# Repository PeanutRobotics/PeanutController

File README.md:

# Peanut Controller

**STM32N657L0 SoM for robotics applications with NN accelerator**

[Board Specification Spreadsheet](https://docs.google.com/spreadsheets/d/1FFwfozj1tVRQfzXSudWjYrMUlAaIKrv69ZutKTBa3as/edit?gid=110133492#gid=110133492)

## Specifications
- 8-layer PCB, 24×40x1 mm, 
- Processor:
    - STM32N6 MCU with Neural-ART accelerator
    - ESP32-C5HF4 for RF, connected to STM32 via UART
- Power:
    - Input: 3.5 ~ 4.3 V (LiPo) via `BAT_IN`
    - 3.3 V power output for external carrier and add-on boards via `3V3_AUX_OUT`
    - INA2227 monitors battery input and auxiliary output
- Onboard sensors:
    - IMU, Magnetometer, Barometer
- Interfaces via Board-to-Board connectors:
    - High speed: USB HS, Ethernet RMII, 2-lane MIPI CSI-2
    - Low speed: UART, I2C, SPI, FDCAN, DShot timer signals
    - Wireless: Wi-Fi 6 (2.4/5 GHz), BLE

## Detailed Specifications
### Processor
| MCU | Flash | RAM | Role | Description |
|-----|-----|-----|-----|-----|
| STM32N657L0H3Q | 128 MiB external OctoSPI NOR | 32 MiB external HexaSPI PSRAM | Main controller | Onboard Neural-ART accelerator |
| ESP32-C5HF4 | 4 MB in-package flash | 400 kB | RF companion | Dual-band Wi-Fi 6 |

### Connectivity
| Type | Name | Domain |
|----------|----------|----------|
| UART     | UART[1:6]  | J3 / J4 |
| SPI      | SPI[2:3]   | J1 / J2 |
| I2C      | I2C[1:3]   | J3 / J4 |
| FDCAN    | FDCAN[1:2] | J1 / J2 |
| DShot    | 8 timer signals (7 shared with UART) | J3 / J4 |
| USB HS   | USB        | J1 / J2 |
| Ethernet | RMII       | J1 / J2 |
| CSI      | MIPI CSI-2 | J5 |
| RF       | Wi-Fi 6 / BLE    | RF      |
| SWD      | SWDIO, SWCLK, NRST, 3.3 V reference, GND | TP1–TP5 |

### Onboard Sensors
| Sensor | Part Name |
|----------|---------|
| IMU          | LSM6DSV16XTR |
| Magnetometer | MMC5983MA |
| Barometer    | BMP581 |
| Power        | INA2227AIYBJR |

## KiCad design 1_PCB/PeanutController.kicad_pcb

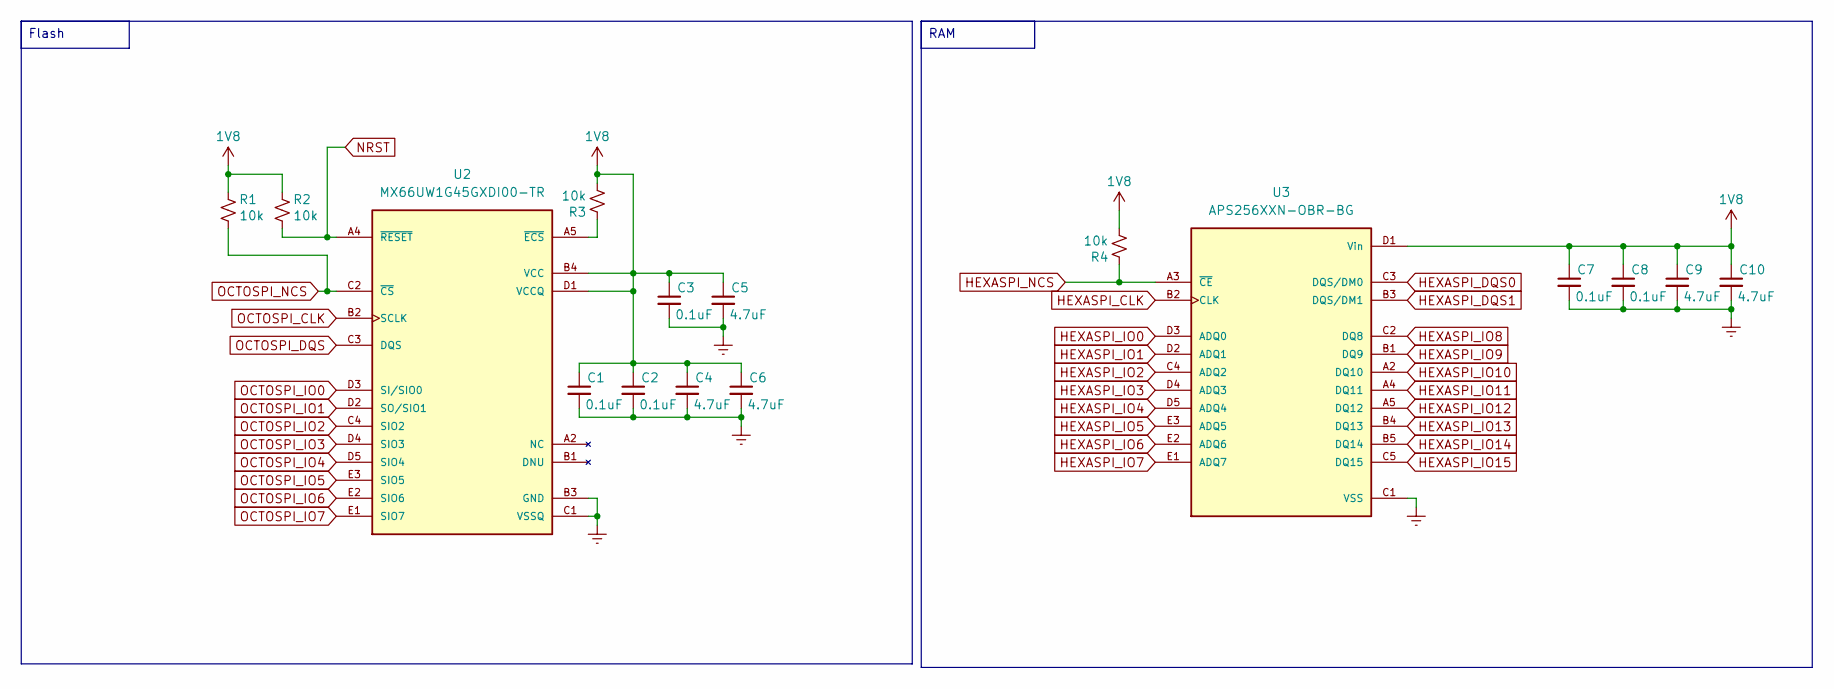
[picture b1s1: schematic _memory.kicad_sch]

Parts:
C1, C2, C3, C7, C8: 0.1uF; C_0402_1005Metric
C4, C5, C6: 4.7uF; C_0603_1608Metric
C9, C10: 4.7uF; C_0402_1005Metric
R1, R2, R3, R4: 10k; R_0402_1005Metric
U2: MX66UW1G45GXDI00-TR; BGA24C100P5X5_800X600X120; PARTREV 1.1
U3: APS256XXN-OBR-BG; BGA24C100P5X5_800X600X120; PARTREV 1.00

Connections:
1V8: C1.1, C2.1, C3.1, C4.1, C5.1, C6.1, C7.1, C8.1, C9.1, C10.1, R1.2, R2.2, R3.1, R4.1, U2.B4 (VCC), U2.D1 (VCCQ), U2.E4 (VCCQ), U3.D1 (Vin), U3.E4 (Vin); also elsewhere on the board
Earth: C1.2, C2.2, C3.2, C4.2, C5.2, C6.2, C7.2, C8.2, C9.2, C10.2, U2.B3 (GND), U2.C1 (VSSQ), U2.E5 (VSSQ), U3.C1 (VSS), U3.E5 (VSS); also elsewhere on the board
HEXASPI_CLK: U3.B2 (CLK); also elsewhere on the board
HEXASPI_DQS0: U3.C3 (DQS/DM0); also elsewhere on the board
HEXASPI_DQS1: U3.B3 (DQS/DM1); also elsewhere on the board
HEXASPI_IO0: U3.D3 (ADQ0); also elsewhere on the board
HEXASPI_IO1: U3.D2 (ADQ1); also elsewhere on the board
HEXASPI_IO2: U3.C4 (ADQ2); also elsewhere on the board
HEXASPI_IO3: U3.D4 (ADQ3); also elsewhere on the board
HEXASPI_IO4: U3.D5 (ADQ4); also elsewhere on the board
HEXASPI_IO5: U3.E3 (ADQ5); also elsewhere on the board
HEXASPI_IO6: U3.E2 (ADQ6); also elsewhere on the board
HEXASPI_IO7: U3.E1 (ADQ7); also elsewhere on the board
HEXASPI_IO8: U3.C2 (DQ8); also elsewhere on the board
HEXASPI_IO9: U3.B1 (DQ9); also elsewhere on the board
HEXASPI_IO10: U3.A2 (DQ10); also elsewhere on the board
HEXASPI_IO11: U3.A4 (DQ11); also elsewhere on the board
HEXASPI_IO12: U3.A5 (DQ12); also elsewhere on the board
HEXASPI_IO13: U3.B4 (DQ13); also elsewhere on the board
HEXASPI_IO14: U3.B5 (DQ14); also elsewhere on the board
HEXASPI_IO15: U3.C5 (DQ15); also elsewhere on the board
HEXASPI_NCS: R4.2, U3.A3 (~CE); also elsewhere on the board
NRST: R2.1, U2.A4 (~RESET); also elsewhere on the board
unnamed: R3.2, U2.A5 (~ECS)
OCTOSPI_CLK: U2.B2 (SCLK); also elsewhere on the board
OCTOSPI_DQS: U2.C3 (DQS); also elsewhere on the board
OCTOSPI_IO0: U2.D3 (SI/SIO0); also elsewhere on the board
OCTOSPI_IO1: U2.D2 (SO/SIO1); also elsewhere on the board
OCTOSPI_IO2: U2.C4 (SIO2); also elsewhere on the board
OCTOSPI_IO3: U2.D4 (SIO3); also elsewhere on the board
OCTOSPI_IO4: U2.D5 (SIO4); also elsewhere on the board
OCTOSPI_IO5: U2.E3 (SIO5); also elsewhere on the board
OCTOSPI_IO6: U2.E2 (SIO6); also elsewhere on the board
OCTOSPI_IO7: U2.E1 (SIO7); also elsewhere on the board
OCTOSPI_NCS: R1.1, U2.C2 (~CS); also elsewhere on the board

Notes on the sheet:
RAM
Flash

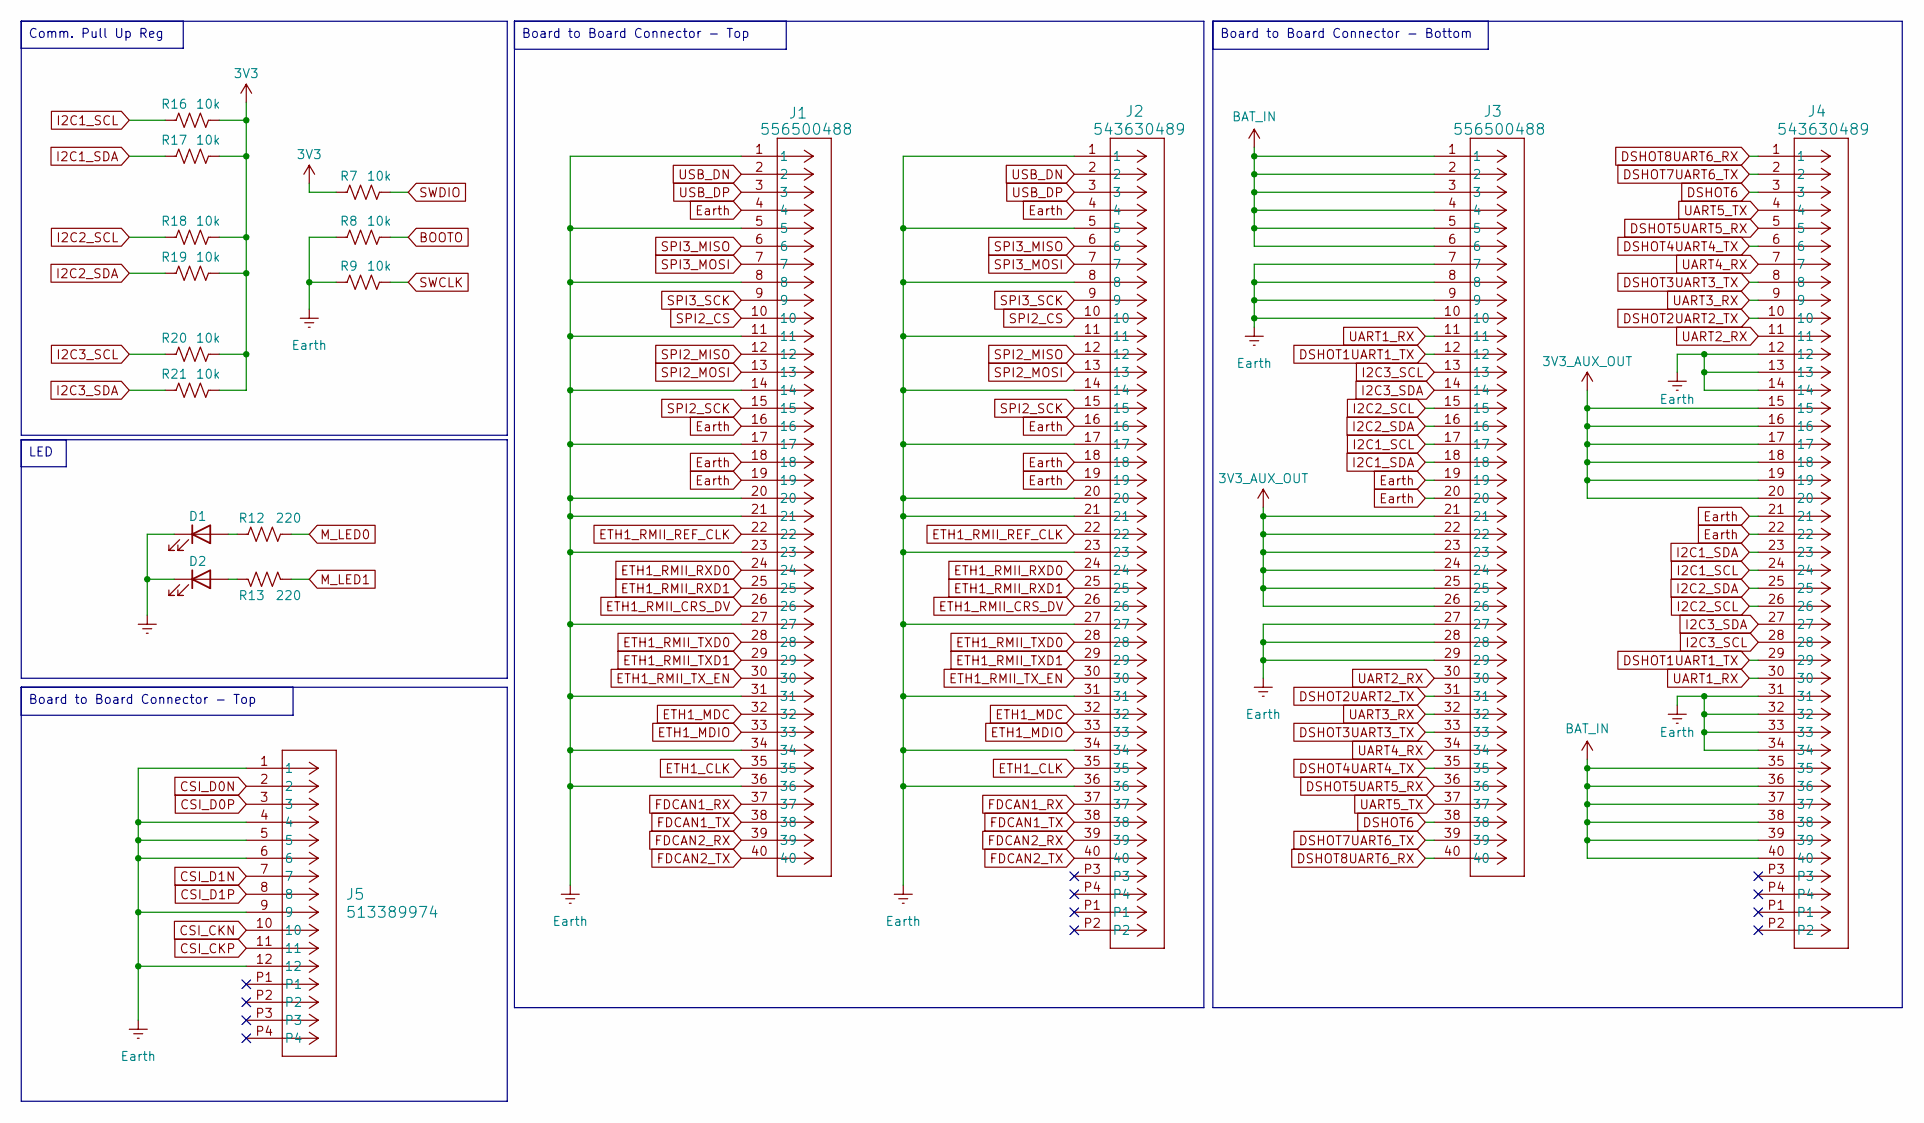
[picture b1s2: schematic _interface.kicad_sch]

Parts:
D1, D2: LED; LED_0603_1608Metric
J1, J3: 556500488; CON_556500488_MOL
J2, J4: 543630489; CON_543630489
J5: 513389974; CON_513389974
R7, R8, R9, R16, R17, R18, R19, R20, R21: 10k; R_0402_1005Metric
R12, R13: 220; R_0402_1005Metric

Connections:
3V3: R7.1, R16.2, R17.2, R18.2, R19.2, R20.2, R21.2; also elsewhere on the board
3V3_AUX_OUT: J3.21, J3.22, J3.23, J3.24, J3.25, J3.26, J4.15, J4.16, J4.17, J4.18, J4.19, J4.20; also elsewhere on the board
BAT_IN: J3.1, J3.2, J3.3, J3.4, J3.5, J3.6, J4.35, J4.36, J4.37, J4.38, J4.39, J4.40; also elsewhere on the board
BOOTO: R8.2; also elsewhere on the board
CSI_CKN: J5.10; also elsewhere on the board
CSI_CKP: J5.11; also elsewhere on the board
CSI_D0N: J5.2; also elsewhere on the board
CSI_D0P: J5.3; also elsewhere on the board
CSI_D1N: J5.7; also elsewhere on the board
CSI_D1P: J5.8; also elsewhere on the board
DSHOT1UART1_TX: J3.12, J4.29; also elsewhere on the board
DSHOT2UART2_TX: J3.31, J4.10; also elsewhere on the board
DSHOT3UART3_TX: J3.33, J4.8; also elsewhere on the board
DSHOT4UART4_TX: J3.35, J4.6; also elsewhere on the board
DSHOT5UART5_RX: J3.36, J4.5; also elsewhere on the board
DSHOT6: J3.38, J4.3; also elsewhere on the board
DSHOT7UART6_TX: J3.39, J4.2; also elsewhere on the board
DSHOT8UART6_RX: J3.40, J4.1; also elsewhere on the board
ETH1_CLK: J1.35, J2.35; also elsewhere on the board
ETH1_MDC: J1.32, J2.32; also elsewhere on the board
ETH1_MDIO: J1.33, J2.33; also elsewhere on the board
ETH1_RMII_CRS_DV: J1.26, J2.26; also elsewhere on the board
ETH1_RMII_REF_CLK: J1.22, J2.22; also elsewhere on the board
ETH1_RMII_RXD0: J1.24, J2.24; also elsewhere on the board
ETH1_RMII_RXD1: J1.25, J2.25; also elsewhere on the board
ETH1_RMII_TXD0: J1.28, J2.28; also elsewhere on the board
ETH1_RMII_TXD1: J1.29, J2.29; also elsewhere on the board
ETH1_RMII_TX_EN: J1.30, J2.30; also elsewhere on the board
Earth: D1.1 (K), D2.1 (K), J1.1, J1.4, J1.5, J1.8, J1.11, J1.14, J1.16, J1.17, J1.18, J1.19, J1.20, J1.21, J1.23, J1.27, J1.31, J1.34, J1.36, J2.1, J2.4, J2.5, J2.8, J2.11, J2.14, J2.16, J2.17, J2.18, J2.19, J2.20, J2.21, J2.23, J2.27, J2.31, J2.34, J2.36, J3.7, J3.8, J3.9, J3.10, J3.19, J3.20, J3.27, J3.28, J3.29, J4.12, J4.13, J4.14, J4.21, J4.22, J4.31, J4.32, J4.33, J4.34, J5.1, J5.4, J5.5, J5.6, J5.9, J5.12, R8.1, R9.1; also elsewhere on the board
FDCAN1_RX: J1.37, J2.37; also elsewhere on the board
FDCAN1_TX: J1.38, J2.38; also elsewhere on the board
FDCAN2_RX: J1.39, J2.39; also elsewhere on the board
FDCAN2_TX: J1.40, J2.40; also elsewhere on the board
I2C1_SCL: J3.17, J4.24, R16.1; also elsewhere on the board
I2C1_SDA: J3.18, J4.23, R17.1; also elsewhere on the board
I2C2_SCL: J3.15, J4.26, R18.1; also elsewhere on the board
I2C2_SDA: J3.16, J4.25, R19.1; also elsewhere on the board
I2C3_SCL: J3.13, J4.28, R20.1; also elsewhere on the board
I2C3_SDA: J3.14, J4.27, R21.1; also elsewhere on the board
M_LED0: R12.2
M_LED1: R13.2
unnamed: D1.2 (A), R12.1
unnamed: D2.2 (A), R13.1
SPI2_CS: J1.10, J2.10; also elsewhere on the board
SPI2_MISO: J1.12, J2.12; also elsewhere on the board
SPI2_MOSI: J1.13, J2.13; also elsewhere on the board
SPI2_SCK: J1.15, J2.15; also elsewhere on the board
SPI3_MISO: J1.6, J2.6; also elsewhere on the board
SPI3_MOSI: J1.7, J2.7; also elsewhere on the board
SPI3_SCK: J1.9, J2.9; also elsewhere on the board
SWCLK: R9.2; also elsewhere on the board
SWDIO: R7.2; also elsewhere on the board
UART1_RX: J3.11, J4.30; also elsewhere on the board
UART2_RX: J3.30, J4.11; also elsewhere on the board
UART3_RX: J3.32, J4.9; also elsewhere on the board
UART4_RX: J3.34, J4.7; also elsewhere on the board
UART5_TX: J3.37, J4.4; also elsewhere on the board
USB_DN: J1.2, J2.2; also elsewhere on the board
USB_DP: J1.3, J2.3; also elsewhere on the board

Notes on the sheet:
Comm. Pull Up Reg
Board to Board Connector - Top
Board to Board Connector - Bottom
LED

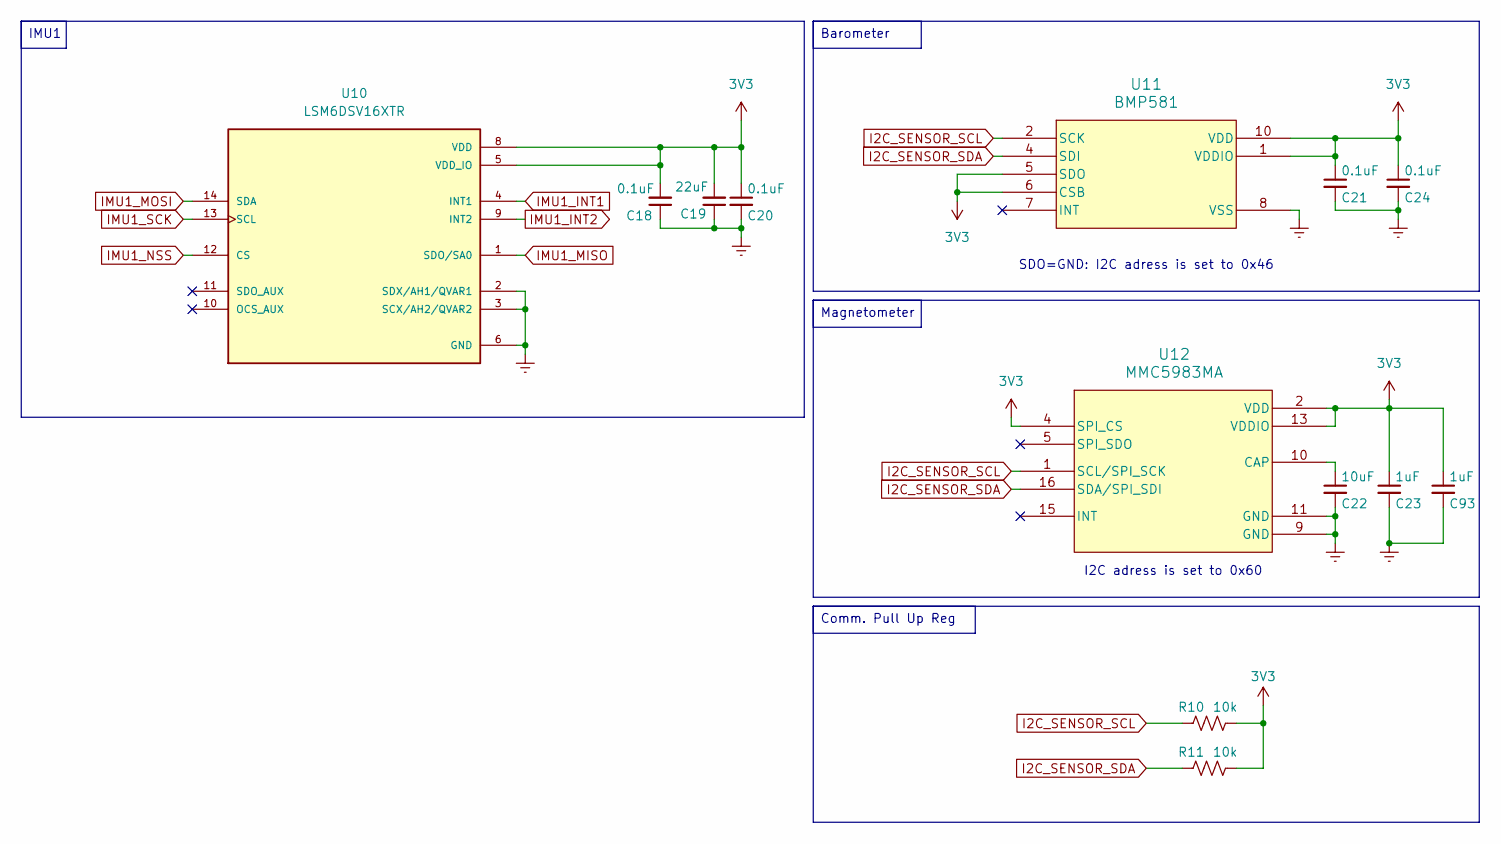
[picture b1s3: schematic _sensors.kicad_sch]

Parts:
C18, C20, C21, C24: 0.1uF; C_0402_1005Metric
C19: 22uF; C_0603_1608Metric
C22: 10uF; C_0402_1005Metric
C23, C93: 1uF; C_0402_1005Metric
R10, R11: 10k; R_0402_1005Metric
U10: LSM6DSV16XTR; XDCR_LSM6DSV16XTR; PARTREV 4
U11: BMP581; QFN10_BMP581_BOS
U12: MMC5983MA; MMC5983MA_MEM

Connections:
3V3: C18.2, C19.2, C20.1, C21.1, C23.1, C24.1, C93.1, R10.2, R11.2, U10.5 (VDD_IO), U10.8 (VDD), U11.1 (VDDIO), U11.5 (SDO), U11.6 (CSB), U11.10 (VDD), U12.2 (VDD), U12.4 (SPI_CS), U12.13 (VDDIO); also elsewhere on the board
Earth: C18.1, C19.1, C20.2, C21.2, C22.2, C23.2, C24.2, C93.2, U10.2 (SDX/AH1/QVAR1), U10.3 (SCX/AH2/QVAR2), U10.6 (GND), U10.7 (GND), U11.3 (VSS), U11.8 (VSS), U11.9 (VSS), U12.9 (GND), U12.11 (GND); also elsewhere on the board
I2C_SENSOR_SCL: R10.1, U11.2 (SCK), U12.1 (SCL/SPI_SCK); also elsewhere on the board
I2C_SENSOR_SDA: R11.1, U11.4 (SDI), U12.16 (SDA/SPI_SDI); also elsewhere on the board
IMU1_INT1: U10.4 (INT1)
IMU1_INT2: U10.9 (INT2); also elsewhere on the board
IMU1_MISO: U10.1 (SDO/SA0); also elsewhere on the board
IMU1_MOSI: U10.14 (SDA); also elsewhere on the board
IMU1_NSS: U10.12 (CS); also elsewhere on the board
IMU1_SCK: U10.13 (SCL); also elsewhere on the board
unnamed: C22.1, U12.10 (CAP)

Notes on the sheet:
I2C adress is set to 0x60
SDO=GND: I2C adress is set to 0x46
IMU1
Comm. Pull Up Reg
Magnetometer
Barometer

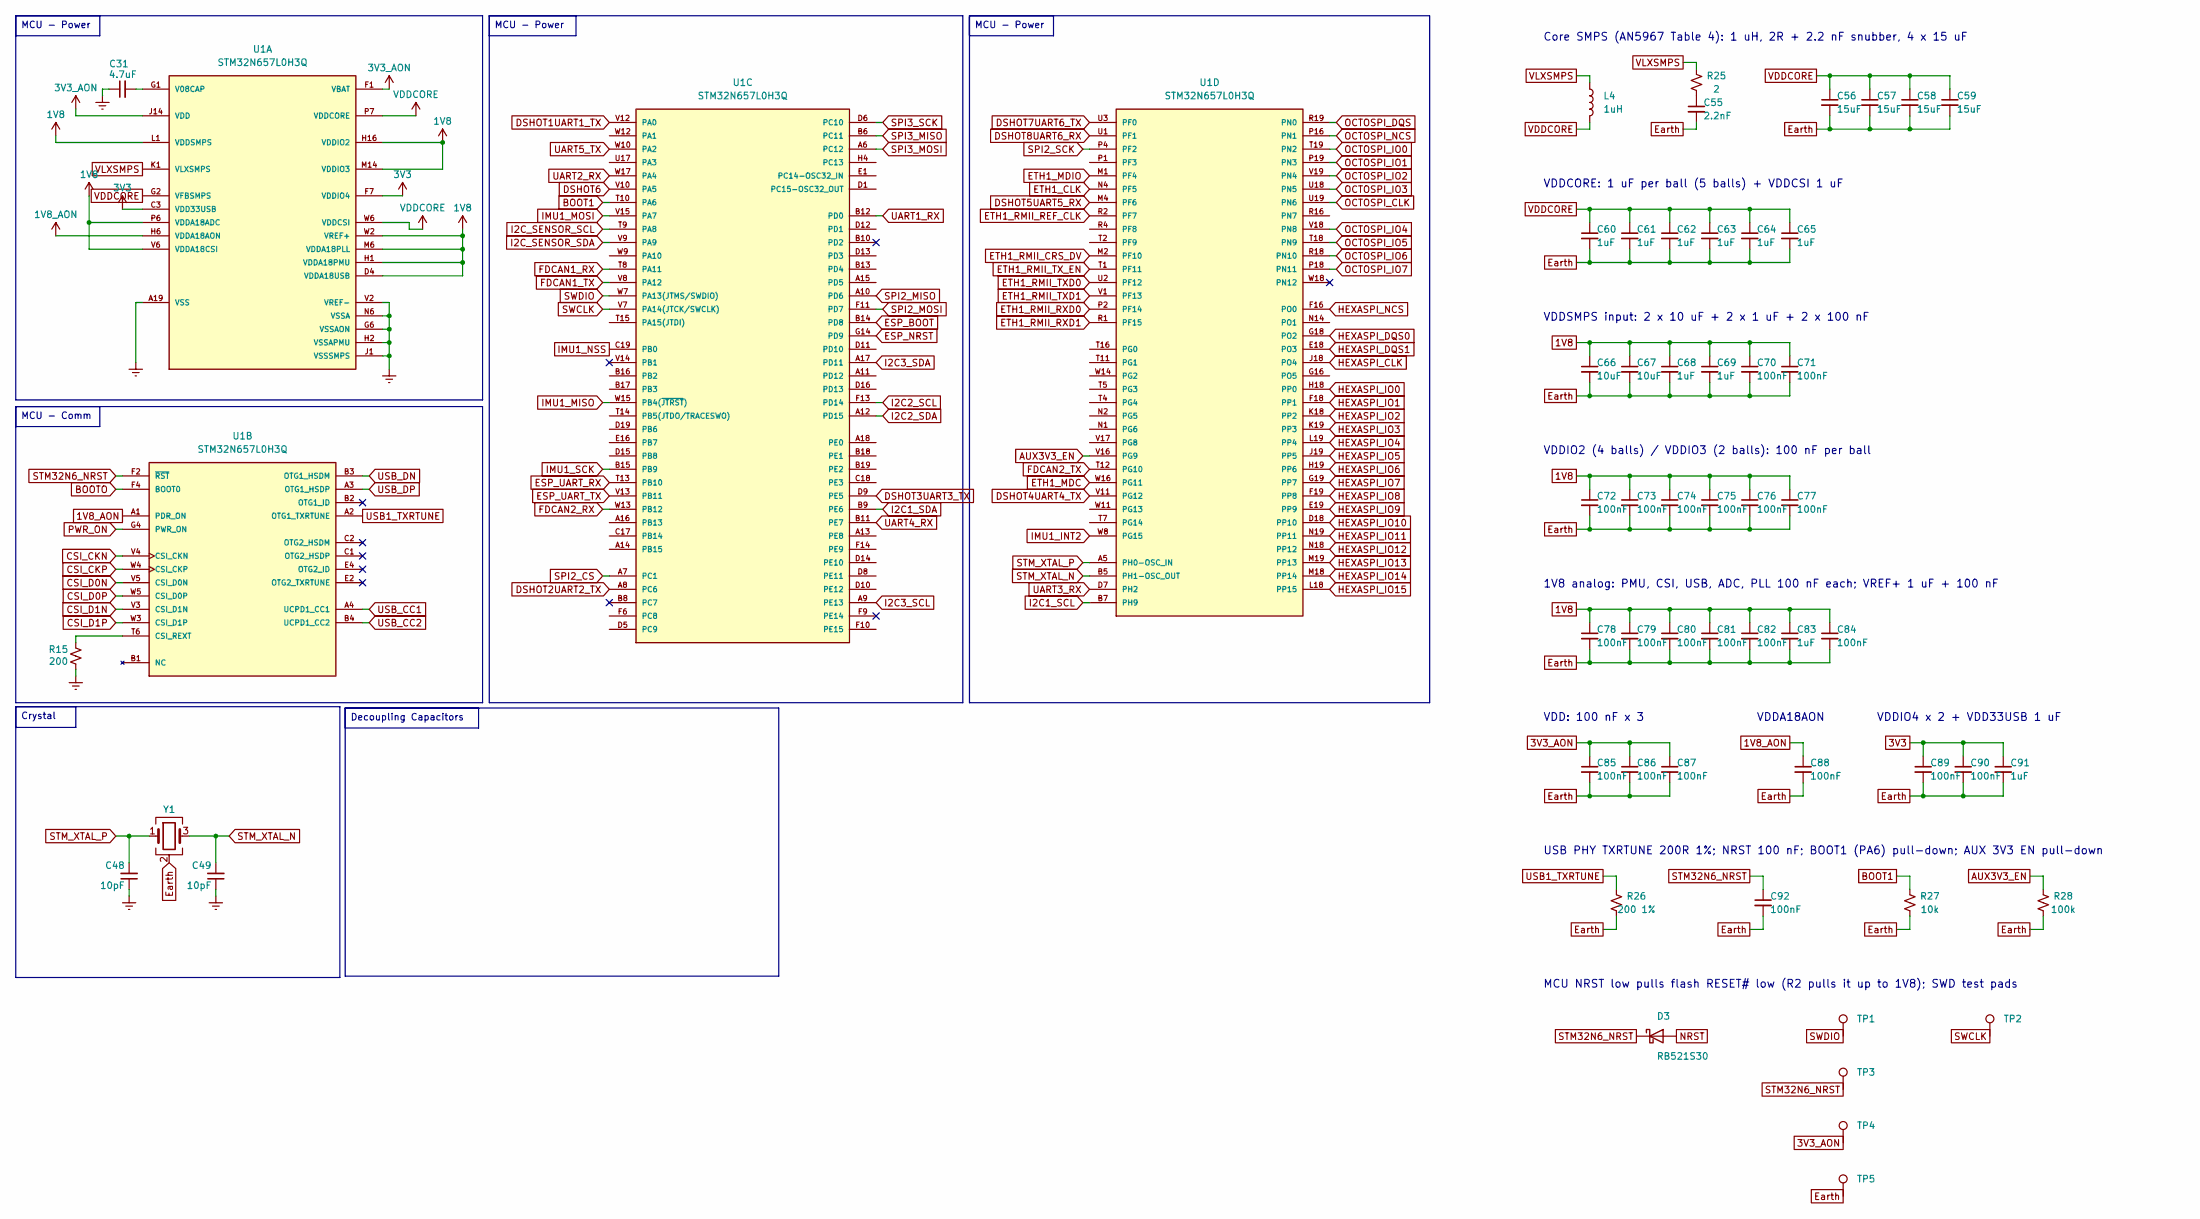
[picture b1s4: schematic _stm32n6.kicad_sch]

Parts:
C31: 4.7uF; C_0402_1005Metric
C48, C49: 10pF; C_0402_1005Metric
C55: 2.2nF; C_0402_1005Metric
C56, C57, C58, C59: 15uF; C_0603_1608Metric
C60, C61, C62, C63, C64, C65, C68, C69, C83, C91: 1uF; C_0201_0603Metric
C66, C67: 10uF; C_0603_1608Metric
C70: 100nF; C_0402_1005Metric
C71, C72, C73, C74, C75, C76, C77, C78, C79, C80, C81, C82, C84, C85, C86, C87, C88, C89, C90, C92: 100nF; C_0201_0603Metric
D3: RB521S30; D_SOD-523
L4: 1uH; L_Murata_DFE201610P
R15: 200; R_0402_1005Metric
R25: 2; R_0402_1005Metric
R26: 200 1%; R_0402_1005Metric
R27: 10k; R_0402_1005Metric
R28: 100k; R_0402_1005Metric
TP1: SWDIO; TestPoint_Pad_D1.0mm
TP2: SWCLK; TestPoint_Pad_D1.0mm
TP3: STM32N6_NRST; TestPoint_Pad_D1.0mm
TP4: 3V3_AON; TestPoint_Pad_D1.0mm
TP5: Earth; TestPoint_Pad_D1.0mm
U1: STM32N657L0H3Q; ST_VFBGA-223_10x10mm_Layout19x19_P0.5mm; PARTREV 2
Y1: 48MHz CL7pF 10ppm; Crystal_NDK_NX2016SA

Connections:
1V8: C66.1, C67.1, C68.1, C69.1, C70.1, C71.1, C72.1, C73.1, C74.1, C75.1, C76.1, C77.1, C78.1, C79.1, C80.1, C81.1, C82.1, C83.1, C84.1, U1.D4 (VDDA18USB), U1.H1 (VDDA18PMU), U1.H16 (VDDIO2), U1.J16 (VDDIO2), U1.K16 (VDDIO2), U1.L1 (VDDSMPS), U1.L2 (VDDSMPS), U1.L3 (VDDSMPS), U1.L4 (VDDSMPS), U1.L5 (VDDSMPS), U1.L16 (VDDIO2), U1.M6 (VDDA18PLL), U1.M14 (VDDIO3), U1.M16 (VDDIO3), U1.P6 (VDDA18ADC), U1.V6 (VDDA18CSI), U1.W2 (VREF+); also elsewhere on the board
1V8_AON: C88.1, U1.A1 (PDR_ON), U1.H6 (VDDA18AON); also elsewhere on the board
3V3: C89.1, C90.1, C91.1, U1.C3 (VDD33USB), U1.F7 (VDDIO4), U1.F8 (VDDIO4); also elsewhere on the board
3V3_AON: C85.1, C86.1, C87.1, TP4.1 (1_1), U1.F1 (VBAT), U1.J14 (VDD), U1.K14 (VDD), U1.L14 (VDD); also elsewhere on the board
AUX3V3_EN: R28.1, U1.V16 (PG9); also elsewhere on the board
BOOT1: R27.1, U1.T10 (PA6)
BOOTO: U1.F4 (BOOT0); also elsewhere on the board
CSI_CKN: U1.V4 (CSI_CKN); also elsewhere on the board
CSI_CKP: U1.W4 (CSI_CKP); also elsewhere on the board
CSI_D0N: U1.V5 (CSI_D0N); also elsewhere on the board
CSI_D0P: U1.W5 (CSI_D0P); also elsewhere on the board
CSI_D1N: U1.V3 (CSI_D1N); also elsewhere on the board
CSI_D1P: U1.W3 (CSI_D1P); also elsewhere on the board
DSHOT1UART1_TX: U1.V12 (PA0); also elsewhere on the board
DSHOT2UART2_TX: U1.A8 (PC6); also elsewhere on the board
DSHOT3UART3_TX: U1.D9 (PE5); also elsewhere on the board
DSHOT4UART4_TX: U1.V11 (PG12); also elsewhere on the board
DSHOT5UART5_RX: U1.M4 (PF6); also elsewhere on the board
DSHOT6: U1.V10 (PA5); also elsewhere on the board
DSHOT7UART6_TX: U1.U3 (PF0); also elsewhere on the board
DSHOT8UART6_RX: U1.U1 (PF1); also elsewhere on the board
ESP_BOOT: U1.B14 (PD8); also elsewhere on the board
ESP_NRST: U1.G14 (PD9); also elsewhere on the board
ESP_UART_RX: U1.T13 (PB10); also elsewhere on the board
ESP_UART_TX: U1.V13 (PB11); also elsewhere on the board
ETH1_CLK: U1.N4 (PF5); also elsewhere on the board
ETH1_MDC: U1.W16 (PG11); also elsewhere on the board
ETH1_MDIO: U1.M1 (PF4); also elsewhere on the board
ETH1_RMII_CRS_DV: U1.M2 (PF10); also elsewhere on the board
ETH1_RMII_REF_CLK: U1.R2 (PF7); also elsewhere on the board
ETH1_RMII_RXD0: U1.P2 (PF14); also elsewhere on the board
ETH1_RMII_RXD1: U1.R1 (PF15); also elsewhere on the board
ETH1_RMII_TXD0: U1.U2 (PF12); also elsewhere on the board
ETH1_RMII_TXD1: U1.V1 (PF13); also elsewhere on the board
ETH1_RMII_TX_EN: U1.T1 (PF11); also elsewhere on the board
Earth: C31.1, C48.1, C49.1, C55.2, C56.2, C57.2, C58.2, C59.2, C60.2, C61.2, C62.2, C63.2, C64.2, C65.2, C66.2, C67.2, C68.2, C69.2, C70.2, C71.2, C72.2, C73.2, C74.2, C75.2, C76.2, C77.2, C78.2, C79.2, C80.2, C81.2, C82.2, C83.2, C84.2, C85.2, C86.2, C87.2, C88.2, C89.2, C90.2, C91.2, C92.2, R15.2, R26.2, R27.2, R28.2, TP5.1 (1_1), U1.A19 (VSS), U1.F12 (VSS), U1.G6 (VSSAON), U1.H2 (VSSAPMU), U1.H14 (VSS), U1.J1 (VSSSMPS), U1.J2 (VSSSMPS), U1.J3 (VSSSMPS), U1.J4 (VSSSMPS), U1.J5 (VSSSMPS), U1.N6 (VSSA), U1.N16 (VSS), U1.P8 (VSS), U1.P12 (VSS), U1.P14 (VSS), U1.V2 (VREF-), U1.W1 (VSS), U1.W19 (VSS), Y1.2 (G), Y1.4 (G); also elsewhere on the board
FDCAN1_RX: U1.T8 (PA11); also elsewhere on the board
FDCAN1_TX: U1.V8 (PA12); also elsewhere on the board
FDCAN2_RX: U1.W13 (PB12); also elsewhere on the board
FDCAN2_TX: U1.T12 (PG10); also elsewhere on the board
HEXASPI_CLK: U1.J18 (PO4); also elsewhere on the board
HEXASPI_DQS0: U1.G18 (PO2); also elsewhere on the board
HEXASPI_DQS1: U1.E18 (PO3); also elsewhere on the board
HEXASPI_IO0: U1.H18 (PP0); also elsewhere on the board
HEXASPI_IO1: U1.F18 (PP1); also elsewhere on the board
HEXASPI_IO2: U1.K18 (PP2); also elsewhere on the board
HEXASPI_IO3: U1.K19 (PP3); also elsewhere on the board
HEXASPI_IO4: U1.L19 (PP4); also elsewhere on the board
HEXASPI_IO5: U1.J19 (PP5); also elsewhere on the board
HEXASPI_IO6: U1.H19 (PP6); also elsewhere on the board
HEXASPI_IO7: U1.G19 (PP7); also elsewhere on the board
HEXASPI_IO8: U1.F19 (PP8); also elsewhere on the board
HEXASPI_IO9: U1.E19 (PP9); also elsewhere on the board
HEXASPI_IO10: U1.D18 (PP10); also elsewhere on the board
HEXASPI_IO11: U1.N19 (PP11); also elsewhere on the board
HEXASPI_IO12: U1.N18 (PP12); also elsewhere on the board
HEXASPI_IO13: U1.M19 (PP13); also elsewhere on the board
HEXASPI_IO14: U1.M18 (PP14); also elsewhere on the board
HEXASPI_IO15: U1.L18 (PP15); also elsewhere on the board
HEXASPI_NCS: U1.F16 (PO0); also elsewhere on the board
I2C1_SCL: U1.B7 (PH9); also elsewhere on the board
I2C1_SDA: U1.B9 (PE6); also elsewhere on the board
I2C2_SCL: U1.F13 (PD14); also elsewhere on the board
I2C2_SDA: U1.A12 (PD15); also elsewhere on the board
I2C3_SCL: U1.A9 (PE13); also elsewhere on the board
I2C3_SDA: U1.A17 (PD11); also elsewhere on the board
I2C_SENSOR_SCL: U1.T9 (PA8); also elsewhere on the board
I2C_SENSOR_SDA: U1.V9 (PA9); also elsewhere on the board
IMU1_INT2: U1.W8 (PG15); also elsewhere on the board
IMU1_MISO: U1.W15 (PB4(~JTRST)); also elsewhere on the board
IMU1_MOSI: U1.V15 (PA7); also elsewhere on the board
IMU1_NSS: U1.C19 (PB0); also elsewhere on the board
IMU1_SCK: U1.B15 (PB9); also elsewhere on the board
NRST: D3.2 (A); also elsewhere on the board
unnamed: C55.1, R25.2
unnamed: C31.2, U1.G1 (V08CAP)
unnamed: R15.1, U1.T6 (CSI_REXT)
OCTOSPI_CLK: U1.U19 (PN6); also elsewhere on the board
OCTOSPI_DQS: U1.R19 (PN0); also elsewhere on the board
OCTOSPI_IO0: U1.T19 (PN2); also elsewhere on the board
OCTOSPI_IO1: U1.P19 (PN3); also elsewhere on the board
OCTOSPI_IO2: U1.V19 (PN4); also elsewhere on the board
OCTOSPI_IO3: U1.U18 (PN5); also elsewhere on the board
OCTOSPI_IO4: U1.V18 (PN8); also elsewhere on the board
OCTOSPI_IO5: U1.T18 (PN9); also elsewhere on the board
OCTOSPI_IO6: U1.R18 (PN10); also elsewhere on the board
OCTOSPI_IO7: U1.P18 (PN11); also elsewhere on the board
OCTOSPI_NCS: U1.P16 (PN1); also elsewhere on the board
PWR_ON: U1.G4 (PWR_ON); also elsewhere on the board
SPI2_CS: U1.A7 (PC1); also elsewhere on the board
SPI2_MISO: U1.A10 (PD6); also elsewhere on the board
SPI2_MOSI: U1.F11 (PD7); also elsewhere on the board
SPI2_SCK: U1.P4 (PF2); also elsewhere on the board
SPI3_MISO: U1.B6 (PC11); also elsewhere on the board
SPI3_MOSI: U1.A6 (PC12); also elsewhere on the board
SPI3_SCK: U1.D6 (PC10); also elsewhere on the board
STM32N6_NRST: C92.1, D3.1 (K), TP3.1 (1_1), U1.F2 (~RST)
STM_XTAL_N: C49.2, U1.B5 (PH1-OSC_OUT), Y1.3
STM_XTAL_P: C48.2, U1.A5 (PH0-OSC_IN), Y1.1
SWCLK: TP2.1 (1_1), U1.V7 (PA14(JTCK/SWCLK)); also elsewhere on the board
SWDIO: TP1.1 (1_1), U1.W7 (PA13(JTMS/SWDIO)); also elsewhere on the board
UART1_RX: U1.B12 (PD0); also elsewhere on the board
UART2_RX: U1.W17 (PA4); also elsewhere on the board
UART3_RX: U1.D7 (PH2); also elsewhere on the board
UART4_RX: U1.B11 (PE7); also elsewhere on the board
UART5_TX: U1.W10 (PA2); also elsewhere on the board
USB1_TXRTUNE: R26.1, U1.A2 (OTG1_TXRTUNE)
USB_CC1: U1.A4 (UCPD1_CC1)
USB_CC2: U1.B4 (UCPD1_CC2)
USB_DN: U1.B3 (OTG1_HSDM); also elsewhere on the board
USB_DP: U1.A3 (OTG1_HSDP); also elsewhere on the board
VDDCORE: C56.1, C57.1, C58.1, C59.1, C60.1, C61.1, C62.1, C63.1, C64.1, C65.1, L4.2, U1.G2 (VFBSMPS), U1.P7 (VDDCORE), U1.P9 (VDDCORE), U1.P10 (VDDCORE), U1.P11 (VDDCORE), U1.P13 (VDDCORE), U1.W6 (VDDCSI)
VLXSMPS: L4.1, R25.1, U1.K1 (VLXSMPS), U1.K2 (VLXSMPS), U1.K3 (VLXSMPS), U1.K4 (VLXSMPS), U1.K5 (VLXSMPS)

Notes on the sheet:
MCU - Power
Crystal
MCU - Comm
Decoupling Capacitors
Core SMPS (AN5967 Table 4): 1 uH, 2R + 2.2 nF snubber, 4 x 15 uF
VDDCORE: 1 uF per ball (5 balls) + VDDCSI 1 uF
VDDSMPS input: 2 x 10 uF + 2 x 1 uF + 2 x 100 nF
VDDIO2 (4 balls) / VDDIO3 (2 balls): 100 nF per ball
1V8 analog: PMU, CSI, USB, ADC, PLL 100 nF each; VREF+ 1 uF + 100 nF
VDD: 100 nF x 3
VDDA18AON
VDDIO4 x 2 + VDD33USB 1 uF
USB PHY TXRTUNE 200R 1%; NRST 100 nF; BOOT1 (PA6) pull-down; AUX 3V3 EN pull-down
MCU NRST low pulls flash RESET# low (R2 pulls it up to 1V8); SWD test pads

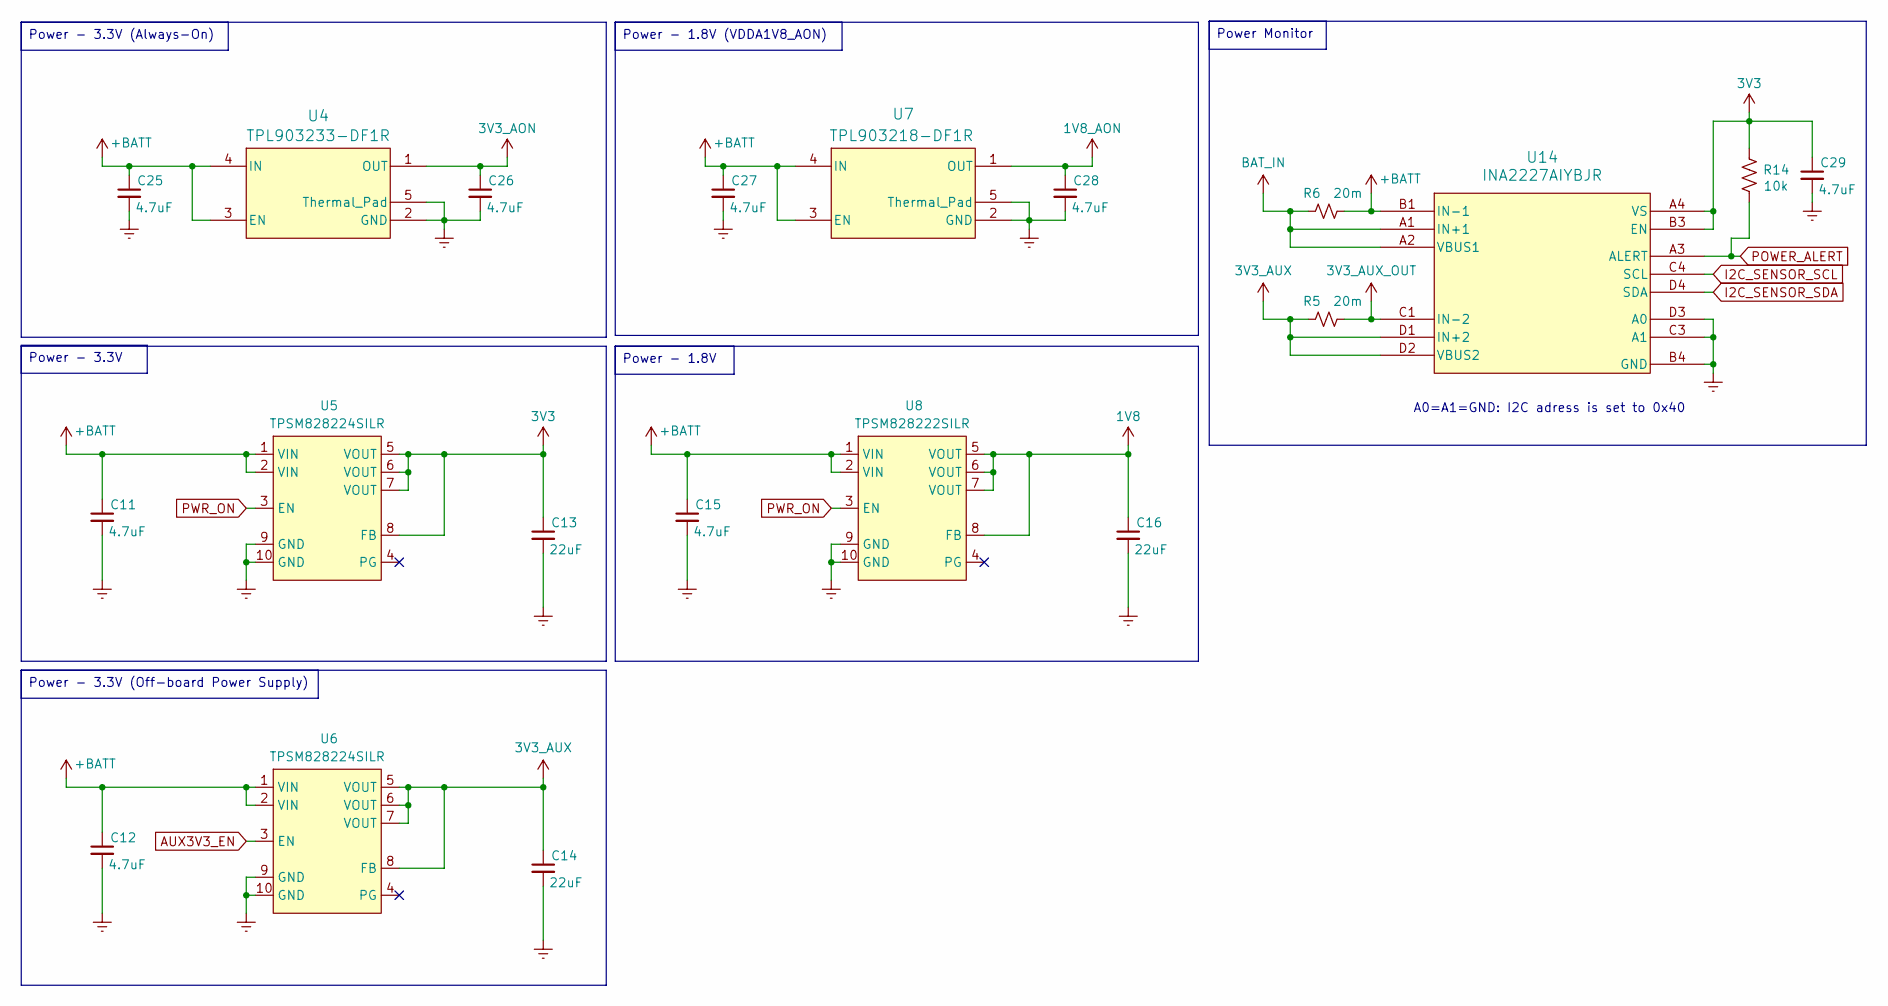
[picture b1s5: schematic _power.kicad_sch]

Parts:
C11, C12, C15: 4.7uF; C_0603_1608Metric
C13, C14, C16: 22uF; C_0603_1608Metric
C25, C26, C27, C28, C29: 4.7uF; C_0402_1005Metric
R5: 20m; R_1206_3216Metric
R6: 20m; R_0612_1632Metric
R14: 10k; R_0402_1005Metric
U4: TPL903233-DF1R; DQN0004A-MFG
U5, U6: TPSM828224SILR; SIL0010D-MFG
U7: TPL903218-DF1R; DQN0004A-MFG
U8: TPSM828222SILR; SIL0010D-MFG
U14: INA2227AIYBJR; U_BGA_YBJ0016-C01_TEX-M

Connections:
1V8: C16.1, U8.5 (VOUT), U8.6 (VOUT), U8.7 (VOUT), U8.8 (FB); also elsewhere on the board
1V8_AON: C28.1, U7.1 (OUT); also elsewhere on the board
3V3: C13.1, C29.1, R14.2, U5.5 (VOUT), U5.6 (VOUT), U5.7 (VOUT), U5.8 (FB), U14.A4 (VS), U14.B3 (EN); also elsewhere on the board
3V3_AON: C26.1, U4.1 (OUT); also elsewhere on the board
3V3_AUX: C14.1, R5.1, U6.5 (VOUT), U6.6 (VOUT), U6.7 (VOUT), U6.8 (FB), U14.D1 (IN+2), U14.D2 (VBUS2)
3V3_AUX_OUT: R5.2, U14.C1 (IN-2); also elsewhere on the board
+BATT: C11.1, C12.1, C15.1, C25.1, C27.1, R6.2, U4.3 (EN), U4.4 (IN), U5.1 (VIN), U5.2 (VIN), U6.1 (VIN), U6.2 (VIN), U7.3 (EN), U7.4 (IN), U8.1 (VIN), U8.2 (VIN), U14.B1 (IN-1)
AUX3V3_EN: U6.3 (EN); also elsewhere on the board
BAT_IN: R6.1, U14.A1 (IN+1), U14.A2 (VBUS1); also elsewhere on the board
Earth: C11.2, C12.2, C13.2, C14.2, C15.2, C16.2, C25.2, C26.2, C27.2, C28.2, C29.2, U4.2 (GND), U4.5 (Thermal_Pad), U5.9 (GND), U5.10 (GND), U6.9 (GND), U6.10 (GND), U7.2 (GND), U7.5 (Thermal_Pad), U8.9 (GND), U8.10 (GND), U14.B4 (GND), U14.C3 (A1), U14.D3 (A0); also elsewhere on the board
I2C_SENSOR_SCL: U14.C4 (SCL); also elsewhere on the board
I2C_SENSOR_SDA: U14.D4 (SDA); also elsewhere on the board
POWER_ALERT: R14.1, U14.A3 (ALERT)
PWR_ON: U5.3 (EN), U8.3 (EN); also elsewhere on the board

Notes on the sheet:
A0=A1=GND: I2C adress is set to 0x40
Power - 3.3V (Always-On)
Power Monitor
Power - 3.3V (Off-board Power Supply)
Power - 1.8V
Power - 1.8V (VDDA1V8_AON)
Power - 3.3V
